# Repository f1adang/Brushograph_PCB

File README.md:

# Brushograph PCB

This repository contains the KiCad PCB design files for the Brushograph (miniPenzlograf) project, a pen-plotting device designed for creating artistic drawings and patterns.

**A manufacturing-ready PCB-design to run FluidNC on ESP32 including ULN2003 drivers for 3 uni-polar stepper motors (28byj-48)**

**A DIY etchable PCB-design to run FluidNC on ESP32 including ULN2003 drivers for 3 uni-polar stepper motors (28byj-48)**

## About Brushograph

This PCB repository is part of the larger Brushograph project, which explores "Ways of painting with a mechatronic brush" - an intersection between classical artistic techniques and modern technology.

**Main Documentation:**
- [Brushograph Wiki](https://wiki.sgmk-ssam.ch/wiki/Brushograph) - Complete project documentation

## Project Structure

- `Brusograf_PCB/` - Original KiCad project (DIY etchable, single layer)
  - `MASK/` - Mask files in SVG and PDF for PCB silkscreen
- `Brushograf_PCB-china/` - Rev A: manufacturing-ready project and Gerbers
  - `Gerber_Brusograf_black.zip` - Zipped Gerbers ready to upload to a PCB manufacturer
- `Brushograf_PCB-revB/` - Rev B: work in progress (see "Rev B" below)
- `FluidNC_config/` - Configuration for FluidNC firmware
  - `config_pink.yaml` - Rev A config
  - `config_revB.yaml` - Rev B config, adds the pendant UART
- `photos/` - Project photos and documentation images

## Rev B (in progress)

`Brushograf_PCB-revB/` replaces the power section with a USB-C Power Delivery
supply feeding an adjustable motor rail, and adds a pendant port and an ESP
power switch.

**Schematic: complete and verified. PCB: all parts placed, routing still to do.**

The board grows from **198 x 48mm to 198 x 73mm** - 25mm added along the top
edge. Everything from rev A keeps its coordinates; all the new parts live in
the new strip. The RJ-12 needs about 19mm of depth behind the top edge and the
old board only had 11mm before the back-side SPI tracks, which is what forced
the growth.

### What rev B adds

**USB-C Power Delivery is now the only power inlet.** The barrel jack is gone,
along with its reverse-polarity FET and zener. J12 sits on the **left edge**
with the receptacle overhanging it; a CH224K sink controller (U6) requests
**9V**, set by the single 6.8k resistor R24 on CFG1 per the WCH datasheet. A
"PD OK" LED (D17) on the controller's power-good output shows when the contract
is up. VBUS reaches the converters through a 1.5A resettable fuse (F1).

PD offers no 7.5V fixed profile, so the 9V rail feeds two buck converters.

**Adjustable motor rail.** U7 (TPS54202, 2A) steps 9V down to the motor rail,
adjustable with trimmer RV1 over roughly **5.4 - 8.6V**, nominally 7.5V. The
divider is 100k on top and 7.5k plus the 10k trimmer below, against the
TPS54202's 0.596V reference. The wiper is tied to the top of the track, so a
lifted wiper drops the output rather than raising it.

> Running 5V-rated 28BYJ-48 motors at 7.5V is a deliberate overclock: about
> 300mA per motor with two phases energised, roughly 900mA for three. More
> torque and speed, but the motors will run noticeably warm. Set the trimmer to
> 5V first and work up.

**Separate 5V logic rail.** U8 (TPS54202) makes 5.07V for the ESP32. The DevKitC
cannot be fed 7.5V on its 5V pin - its onboard AMS1117 would burn about a watt -
so logic and motors get separate rails.

**ESP power switch.** SW1 is a panel **lever switch on the left edge**, actuator
overhanging the board. It is a 1P2T part used as a simple break: common to the
ESP32, one throw to the board's 5V, the other left open, so the far position
leaves the module running on its own USB supply while the rest of the board
stays powered. D14 (SS14) blocks USB 5V from back-feeding the logic buck.

**RJ-12 pendant port** on the **upper edge**, opening facing off the board. J13
brings UART1 out on GPIO 2 and 15 with switched 5V, behind a 0.5A resettable
fuse (F2), 330R series resistors and TVS clamps.

**J7 repurposed.** Pin 3 used to carry the raw barrel-jack rail straight to the
motors, which would have destroyed them with a 12V adapter. It now carries the
regulated adjustable rail; pin 1 is the 5V logic rail for testing, pin 2 the
motor rail.

### Status

| Area | State |
|---|---|
| Schematic | Complete. 75 parts, 120 nets, netlist verified net by net |
| ERC | At or below rev A in every category |
| Placement | All 36 new footprints placed, zones refilled |
| DRC | No new errors except on J12 - see below |
| Routing | **53 ratsnest connections outstanding** |

### Known DRC findings

- **J12 reports 27 `shorting_items` and 4 `hole_clearance` errors.** These are
  not caused by the placement: the same 31 errors appear with the untouched
  stock footprint alone on an otherwise empty board. The pads have genuine
  0.2-0.7mm gaps and nothing bridges them - zones, solder mask and neighbouring
  copper were each ruled out by experiment. Every USB-C footprint in the KiCad
  library has sub-0.25mm pad gaps, so swapping parts will not help. Worth
  opening in the GUI, where the marker shows interactively what it thinks is
  touching, before committing to fab.
- `allow_soldermask_bridges` is set on J12, which is the correct treatment for a
  fine-pitch connector and clears 23 mask-bridge errors.
- Everything else - 4 mounting-hole annular widths, U4's malformed courtyard,
  5 starved thermals - is inherited unchanged from rev A.

### Open questions

- **The RJ-12 pin order is unverified.** The board uses
  `1 = GND, 2 = +5V, 3 = TX, 4 = RX, 5 = +5V, 6 = GND`, chosen so a standard
  reversing modular cable keeps power and ground on the right contacts and swaps
  TX/RX. bdring's official FluidDial pinout could not be confirmed from public
  documentation - **check it against your cable before building**.
- GPIO2 is an ESP32 strapping pin. It must not be pulled high during boot or the
  chip enters download mode. An idle-high UART receiver at the pendant end is
  fine; anything that actively drives the line is not.

### Known issues carried over from rev A

- The `MISO` and `MOSI` net names are swapped relative to the SD card: net
  `MISO` (GPIO19) goes to the card's CMD/DI pin, which is physically MOSI. The
  card works and the FluidNC config is correct, but **J6's back silkscreen is
  mislabelled** - an external SD module wired to J6 per the silk will have DI
  and DO reversed.
- R1-R12 and C1-C3 still have no values in the schematic, so the BOM is not
  directly orderable.
- The four mounting holes are plated pads with zero annular ring and should be
  non-plated.

## Features

- Custom PCB design for the Brushograph device
- ESP32-based control board with FluidNC firmware support
- Integrated ULN2003 drivers for 3 uni-polar stepper motors (28byj-48)
- DIY etchable single-layer design for easy home fabrication
- Rounded PCB version available
- Configuration files for FluidNC firmware (custom fork for support uni-polar steppers)

## Hardware Configuration

### ESP32 Pin Configuration

Phase order below matches `FluidNC_config/config_revB.yaml`. Note it is the
reverse of what older revisions of this README listed - reversing the phase
order simply reverses the direction of travel.

#### X-Axis Motor (Unipolar)
- Phase 0: GPIO 27
- Phase 1: GPIO 14
- Phase 2: GPIO 13
- Phase 3: GPIO 4

#### Y-Axis Motor (Unipolar)
- Phase 0: GPIO 22
- Phase 1: GPIO 21
- Phase 2: GPIO 17
- Phase 3: GPIO 16

#### Z-Axis Motor (Unipolar)
- Phase 0: GPIO 32
- Phase 1: GPIO 33
- Phase 2: GPIO 25
- Phase 3: GPIO 26

#### SD Card (SPI)
- MOSI: GPIO 19  (net labelled `MISO` on the schematic - see Known issues)
- MISO: GPIO 23  (net labelled `MOSI` on the schematic - see Known issues)
- SCK: GPIO 18
- CS: GPIO 5

#### Pendant UART (rev B)
- TX: GPIO 2 (J13)
- RX: GPIO 15 (J13)

#### Still free
GPIO 34, 35, 36 and 39 (all input-only), GPIO 12, and UART0 on GPIO 1/3.

The four input-only pins are the natural place for limit switches if homing is
added later; they have no internal pull-ups, so each would need an external one.

### Motor Configuration

`config_revB.yaml` in the FluidNC_config directory carries the settings for the
stepper motors. There are no limit switches, so no homing cycles are defined and
every limit pin is `NO_PIN`:

- X/Y axis: 93 steps/mm, 1500 mm/min max rate, 80 mm/s2 acceleration
- Z axis: 108 steps/mm, 1000 mm/min max rate, 40 mm/s2 acceleration

### 28BYJ-48 Stepper Motors

The PCB is designed specifically for the commonly available and inexpensive 28BYJ-48 unipolar stepper motors:
- 5V DC operation
- Gear reduction ratio of 1:64
- Step angle of 5.625° (64 steps per revolution)
- 4-phase operation via ULN2003 driver

## Getting Started

To view or modify the PCB design:
1. Install KiCad (version 6.0 or later recommended)
2. Open the `.kicad_pro` project file in the `Brusograf_PCB` directory
     - For the latest manufacturing-ready version, you can also open the project in `Brushograf_PCB-china/`

For complete setup instructions, including firmware and mechanical assembly, please refer to the [Brushograph Wiki](https://wiki.sgmk-ssam.ch/wiki/Brushograph).

## Manufacturing-ready files

- Latest Gerbers (ZIP, ready for fab): [`Brushograf_PCB-china/Gerber_Brusograf_black.zip`](Brushograf_PCB-china/Gerber_Brusograf_black.zip)
- Gerber folder (all layers and drill files): [`Brushograf_PCB-china/Gerber_Brusograf/`](Brushograf_PCB-china/Gerber_Brusograf/)

## Related Repositories

- [FluidNC for unipolar steppers](https://git.kompot.si/g1smo/FluidNC) - Forked and reworked version of FluidNC to support uni-polar steppers

## License

[Specify license here]

## Credits

Designed by dusjagr

The Brushograph project is based on Dominik Mahnič's "Brušografia" concept, bridging traditional painting and technology.

## Contact

[Your contact information here]

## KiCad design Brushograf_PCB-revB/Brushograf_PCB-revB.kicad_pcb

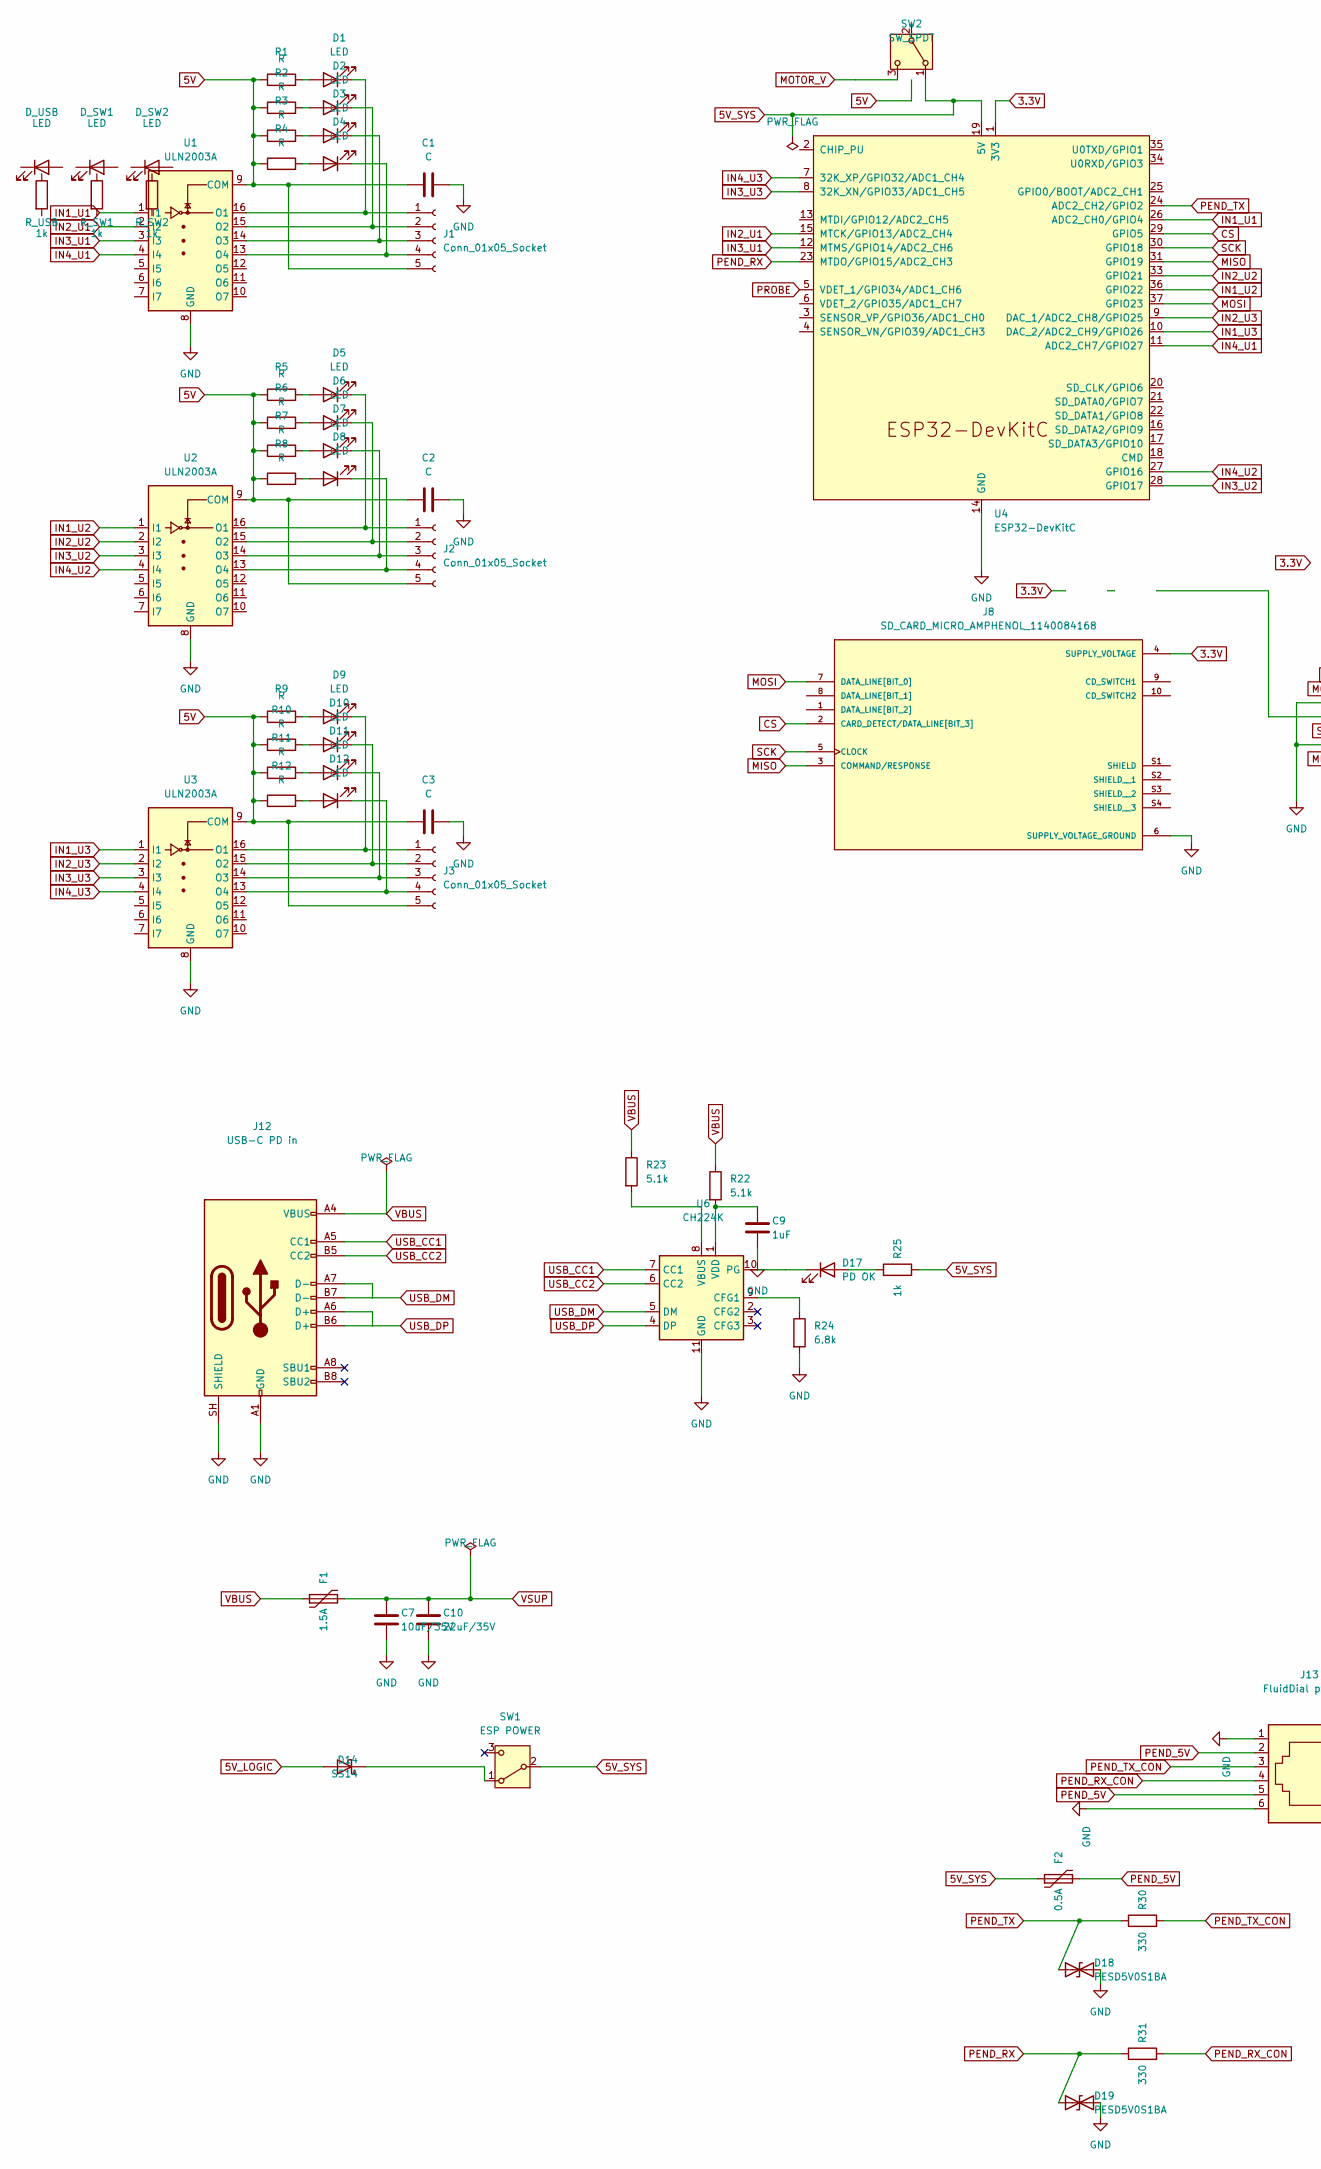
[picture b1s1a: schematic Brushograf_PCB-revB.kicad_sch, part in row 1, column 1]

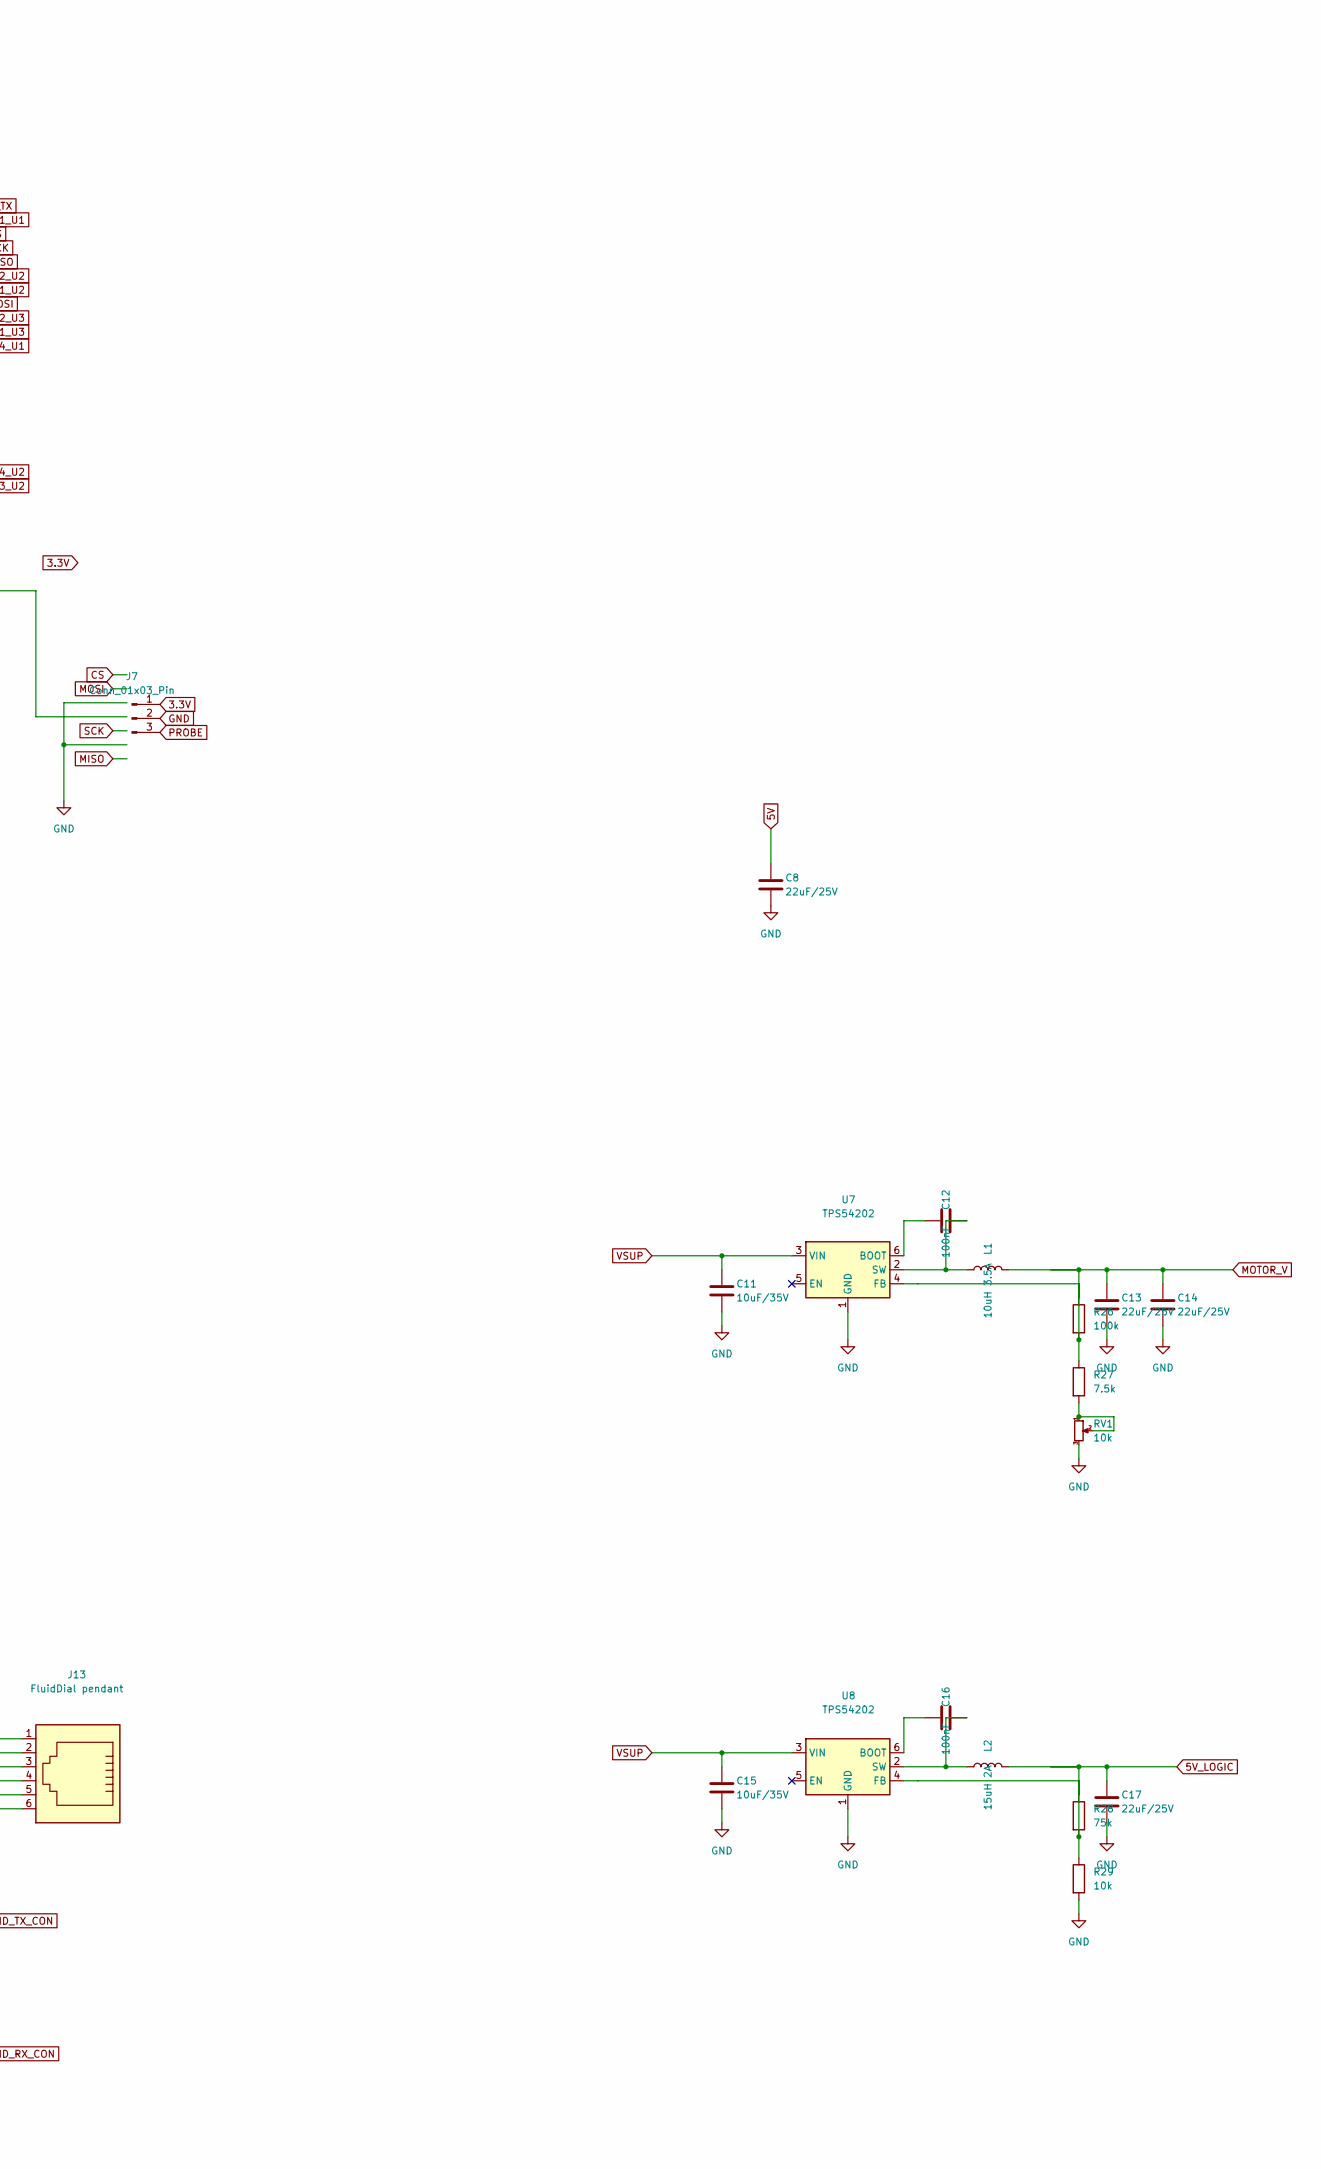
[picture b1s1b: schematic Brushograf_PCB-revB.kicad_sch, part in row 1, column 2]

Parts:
C1, C2, C3: C; C_1210_noGND
C7: 10uF/35V; C_1206_3216Metric_Pad1.33x1.80mm_HandSolder
C8, C13, C14, C17: 22uF/25V; C_1210_3225Metric_Pad1.33x2.70mm_HandSolder
C9: 1uF; C_0603_1608Metric_Pad1.08x0.95mm_HandSolder
C10: 22uF/35V; C_1210_3225Metric_Pad1.33x2.70mm_HandSolder
C11, C15: 10uF/35V; C_1210_3225Metric_Pad1.33x2.70mm_HandSolder
C12, C16: 100nF; C_0603_1608Metric_Pad1.08x0.95mm_HandSolder
D1, D2, D3, D4, D5, D6, D7, D8, D9, D10, D11, D12: LED; LED_D1.8mm_W3.3mm_H2.4mm
D14: SS14; D_SMA_Handsoldering
D17: PD OK; LED_0805_2012Metric_Pad1.15x1.40mm_HandSolder
D18, D19: PESD5V0S1BA; D_SOD-323
D_SW1, D_SW2: LED; LED_D1.8mm_Brushograf
D_USB: LED; LED_D1.8mm_Brushograf
F1: 1.5A; Fuse_1812_4532Metric_Pad1.30x3.40mm_HandSolder
F2: 0.5A; Fuse_1206_3216Metric_Pad1.42x1.75mm_HandSolder
J1, J2, J3: Conn_01x05_Socket; Molex_1x05_P2.54mm_Vertical
J7: Conn_01x03_Pin; PinHeader_1x03_P2.54mm_Vertical
J8: SD_CARD_MICRO_AMPHENOL_1140084168; PARTREV A
J12: USB-C PD in; USB_C_Receptacle_GCT_USB4105-xx-A_16P_TopMnt_Horizontal
J13: FluidDial pendant; RJ12_Amphenol_54601-x06_Horizontal
L1: 10uH 3.5A; L_7.3x7.3_H4.5
L2: 15uH 2A; L_7.3x7.3_H4.5
R1, R2, R3, R4, R5, R6, R7, R8, R9, R10, R11, R12: R; R_1206_noGND
R22, R23: 5.1k; R_0603_1608Metric_Pad0.98x0.95mm_HandSolder
R24: 6.8k; R_0603_1608Metric_Pad0.98x0.95mm_HandSolder
R25: 1k; R_0603_1608Metric_Pad0.98x0.95mm_HandSolder
R26: 100k; R_0603_1608Metric_Pad0.98x0.95mm_HandSolder
R27: 7.5k; R_0603_1608Metric_Pad0.98x0.95mm_HandSolder
R28: 75k; R_0603_1608Metric_Pad0.98x0.95mm_HandSolder
R29: 10k; R_0603_1608Metric_Pad0.98x0.95mm_HandSolder
R30, R31: 330; R_0603_1608Metric_Pad0.98x0.95mm_HandSolder
RV1: 10k; Potentiometer_Bourns_3296W_Vertical
R_SW1, R_SW2: 1k; R_1206_noGND
R_USB: 1k; R_1206_noGND
SW1: ESP POWER; SW_Lever_1P2T_NKK_GW12LxH
SW2: SW_SPDT; SW_Slide_1P2T_EG1218
U1, U2, U3: ULN2003A; DIP-16_W7.62mm_Socket_LongPads
U4: ESP32-DevKitC; ESP32-DevKitC_mod
U6: CH224K; SSOP-10-1EP_3.9x4.9mm_P1mm_EP2.1x3.3mm
U7, U8: TPS54202; SOT-23-6

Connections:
3.3V: J7.1, J8.4 (SUPPLY_VOLTAGE), U4.1 (3V3)
5V: C1.1, C2.1, C3.1, C8.1, J1.5, J2.5, J3.5, R1.1, R2.1, R3.1, R4.1, R5.1, R6.1, R7.1, R8.1, R9.1, R10.1, R11.1, R12.1, R_SW2.1, SW2.2 (B), U1.9 (COM), U2.9 (COM), U3.9 (COM); also elsewhere on the board
5V_LOGIC: C17.1, D14.2 (A), L2.2, R28.1; also elsewhere on the board
5V_SYS: F2.1, R25.2, R_SW1.1, SW1.2 (B), SW2.1 (A), U4.19 (5V)
CS: J8.2 (CARD_DETECT/DATA_LINE[BIT_3]), U4.29 (GPIO5)
GND: C1.2, C2.2, C3.2, C7.2, C8.2, C9.2, C10.2, C11.2, C13.2, C14.2, C15.2, C17.2, D18.2 (A2), D19.2 (A2), D_SW1.2 (A), D_SW2.2 (A), D_USB.2 (A), J7.2, J8.6 (SUPPLY_VOLTAGE_GROUND), J12.A1 (GND), J12.A12 (GND), J12.B1 (GND), J12.B12 (GND), J12.SH (SHIELD), J13.1, J13.6, R24.2, R29.2, RV1.3, U1.8 (GND), U2.8 (GND), U3.8 (GND), U4.14 (GND), U4.32 (GND), U4.38 (GND), U6.11 (GND), U7.1 (GND), U8.1 (GND); also elsewhere on the board
IN1_U1: U1.1 (I1), U4.26 (ADC2_CH0/GPIO4); also elsewhere on the board
IN1_U2: U2.1 (I1), U4.36 (GPIO22); also elsewhere on the board
IN1_U3: U3.1 (I1), U4.10 (DAC_2/ADC2_CH9/GPIO26); also elsewhere on the board
IN2_U1: U1.2 (I2), U4.15 (MTCK/GPIO13/ADC2_CH4); also elsewhere on the board
IN2_U2: U2.2 (I2), U4.33 (GPIO21); also elsewhere on the board
IN2_U3: U3.2 (I2), U4.9 (DAC_1/ADC2_CH8/GPIO25); also elsewhere on the board
IN3_U1: U1.3 (I3), U4.12 (MTMS/GPIO14/ADC2_CH6); also elsewhere on the board
IN3_U2: U2.3 (I3), U4.28 (GPIO17); also elsewhere on the board
IN3_U3: U3.3 (I3), U4.8 (32K_XN/GPIO33/ADC1_CH5); also elsewhere on the board
IN4_U1: U1.4 (I4), U4.11 (ADC2_CH7/GPIO27); also elsewhere on the board
IN4_U2: U2.4 (I4), U4.27 (GPIO16); also elsewhere on the board
IN4_U3: U3.4 (I4), U4.7 (32K_XP/GPIO32/ADC1_CH4); also elsewhere on the board
MISO: J8.3 (COMMAND/RESPONSE), U4.31 (GPIO19)
MOSI: J8.7 (DATA_LINE[BIT_0]), U4.37 (GPIO23)
unnamed: D1.1 (K), J1.1, U1.16 (O1)
unnamed: D2.2 (A), R2.2
unnamed: D2.1 (K), J1.2, U1.15 (O2)
unnamed: D3.2 (A), R3.2
unnamed: D3.1 (K), J1.3, U1.14 (O3)
unnamed: D4.2 (A), R4.2
unnamed: D4.1 (K), J1.4, U1.13 (O4)
unnamed: D5.2 (A), R5.2
unnamed: D5.1 (K), J2.1, U2.16 (O1)
unnamed: D6.2 (A), R6.2
unnamed: D6.1 (K), J2.2, U2.15 (O2)
unnamed: D7.2 (A), R7.2
unnamed: D7.1 (K), J2.3, U2.14 (O3)
unnamed: D8.2 (A), R8.2
unnamed: D8.1 (K), J2.4, U2.13 (O4)
unnamed: D9.2 (A), R9.2
unnamed: D9.1 (K), J3.1, U3.16 (O1)
unnamed: D10.2 (A), R10.2
unnamed: D10.1 (K), J3.2, U3.15 (O2)
unnamed: D11.2 (A), R11.2
unnamed: D11.1 (K), J3.3, U3.14 (O3)
unnamed: D12.2 (A), R12.2
unnamed: D12.1 (K), J3.4, U3.13 (O4)
unnamed: D14.1 (K), SW1.1 (A)
unnamed: D17.2 (A), R25.1
unnamed: D17.1 (K), U6.10 (PG)
unnamed: D_SW1.1 (K), R_SW1.2
unnamed: D_SW2.1 (K), R_SW2.2
unnamed: D_USB.1 (K), R_USB.2
unnamed: R27.2, RV1.1, RV1.2
unnamed: R24.1, U6.9 (CFG1)
unnamed: R23.2, U6.8 (VBUS)
unnamed: C9.1, R22.2, U6.1 (VDD)
unnamed: C12.1, U7.6 (BOOT)
unnamed: R26.2, R27.1, U7.4 (FB)
unnamed: C12.2, L1.1, U7.2 (SW)
unnamed: C16.1, U8.6 (BOOT)
unnamed: R28.2, R29.1, U8.4 (FB)
unnamed: C16.2, L2.1, U8.2 (SW)
PEND_5V: F2.2, J13.2, J13.5
PEND_RX: D19.1 (A1), R31.1, U4.23 (MTDO/GPIO15/ADC2_CH3)
PEND_RX_CON: J13.4, R31.2
PEND_TX: D18.1 (A1), R30.1, U4.24 (ADC2_CH2/GPIO2)
PEND_TX_CON: J13.3, R30.2
PROBE: J7.3, U4.5 (VDET_1/GPIO34/ADC1_CH6)
SCK: J8.5 (CLOCK), U4.30 (GPIO18)
USB_CC1: J12.A5 (CC1), U6.7 (CC1)
USB_CC2: J12.B5 (CC2), U6.6 (CC2)
USB_DM: J12.A7 (D-), J12.B7 (D-), U6.5 (DM)
USB_DP: J12.A6 (D+), J12.B6 (D+), U6.4 (DP)
VBUS: F1.1, J12.A4 (VBUS), J12.A9 (VBUS), J12.B4 (VBUS), J12.B9 (VBUS), R22.1, R23.1, R_USB.1
VSUP: C7.1, C10.1, C11.1, C15.1, F1.2, U7.3 (VIN), U8.3 (VIN)

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
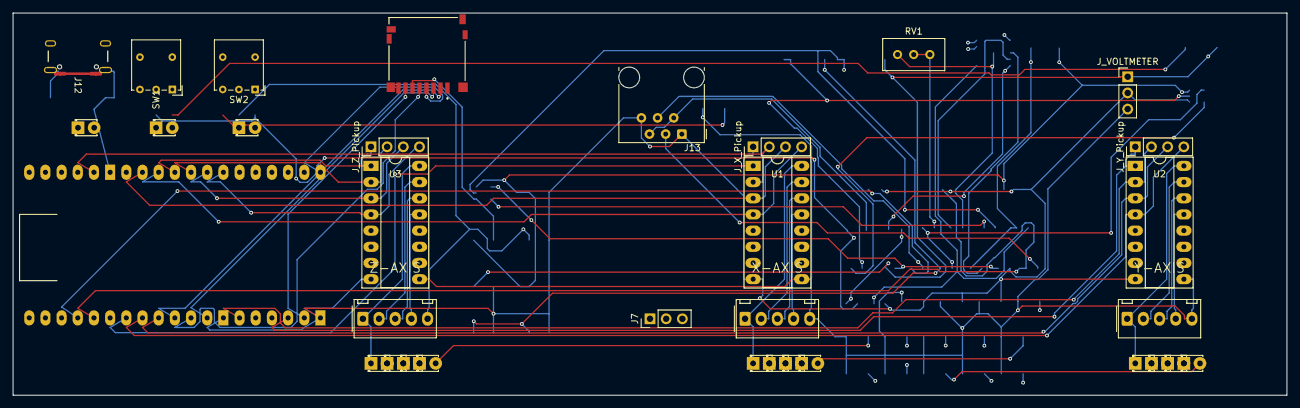
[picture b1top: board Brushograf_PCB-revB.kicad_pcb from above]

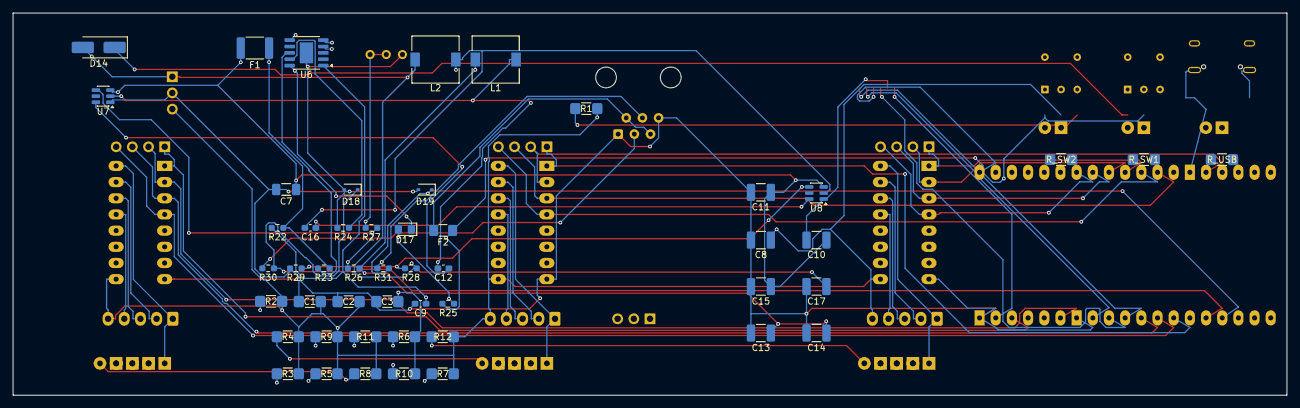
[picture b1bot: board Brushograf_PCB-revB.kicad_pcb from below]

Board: 2 copper layers, 200.0 x 60.0 mm, 83 parts (50 on the bottom side), 73 nets.

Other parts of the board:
J_VOLTMETER: PinHeader_1x03_P2.54mm_Vertical
J_X_Pickup: PinHeader_1x04_P2.54mm_Vertical
J_Y_Pickup: PinHeader_1x04_P2.54mm_Vertical
J_Z_Pickup: PinHeader_1x04_P2.54mm_Vertical

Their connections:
5V: J_VOLTMETER.3; also elsewhere on the board
5V_LOGIC: J_VOLTMETER.1; also elsewhere on the board
GND: J_VOLTMETER.2; also elsewhere on the board
IN1_U1: J_X_Pickup.1; also elsewhere on the board
IN1_U2: J_Y_Pickup.1; also elsewhere on the board
IN1_U3: J_Z_Pickup.1; also elsewhere on the board
IN2_U1: J_X_Pickup.2; also elsewhere on the board
IN2_U2: J_Y_Pickup.2; also elsewhere on the board
IN2_U3: J_Z_Pickup.2; also elsewhere on the board
IN3_U1: J_X_Pickup.3; also elsewhere on the board
IN3_U2: J_Y_Pickup.3; also elsewhere on the board
IN3_U3: J_Z_Pickup.3; also elsewhere on the board
IN4_U1: J_X_Pickup.4; also elsewhere on the board
IN4_U2: J_Y_Pickup.4; also elsewhere on the board
IN4_U3: J_Z_Pickup.4; also elsewhere on the board

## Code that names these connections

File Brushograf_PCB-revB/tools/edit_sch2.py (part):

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    raise SystemExit('ERROR: J7 5V-EXT label not found')

# pendant UART out to the ESP32
sh.wire(157.48, 57.15, 152.4, 57.15)          # U4 pin 23, GPIO15
sh.label('PEND_RX', 152.4, 57.15, 180)
sh.wire(223.52, 46.99, 228.6, 46.99)          # U4 pin 24, GPIO2
sh.label('PEND_TX', 228.6, 46.99, 0)

# =====================================================  USB-C + CH224K PD sink
J12 = sh.place('Connector', 'USB_C_Receptacle_USB2.0_16P', 'J12', 'USB-C PD in',
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sh.junction(97.79, YB)
sh.wire(97.79, YB, 97.79, YB - 7.62)
sh.pwrflag(97.79, YB - 7.62, 0)
sh.label('VSUP', 105.0, YB, 0)

# =====================================================  buck converters
def buck(ref_u, X, Y, vout_net, l_ref, l_val, cin_ref, cb_ref, cout_refs,
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                 ref_at=(X, Y - 12.7, None), val_at=(X, Y - 10.16, None))
    vin = U.p('VIN')
    sh.wire(vin[0] - 25.4, vin[1], *vin)
    sh.label('VSUP', vin[0] - 25.4, vin[1], 180)
    Cin = sh.place('Device', 'C', cin_ref, cin_val, C1210, vin[0] - 12.7, vin[1] + 6.35, 0)
    sh.wire(vin[0] - 12.7, vin[1], *Cin.p('1'))
    sh.junction(vin[0] - 12.7, vin[1])
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YP = 330.0
J13 = sh.place('Connector', 'RJ12', 'J13', 'FluidDial pendant', RJ12FP, 250, YP, 180,
               ref_at=(250, YP - 16.51, None), val_at=(250, YP - 13.97, None))
PEND_PINS = [('1', 'GND', 5.08), ('2', 'PEND_5V', 10.16), ('3', 'PEND_TX_CON', 15.24),
             ('4', 'PEND_RX_CON', 20.32), ('5', 'PEND_5V', 25.4), ('6', 'GND', 30.48)]
for pin, net, ln in PEND_PINS:
    px, py = J13.p(pin)
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sh.wire(F2.p('1')[0] - 7.62, F2.p('1')[1], *F2.p('1'))
sh.label('5V_SYS', F2.p('1')[0] - 7.62, F2.p('1')[1], 180)
sh.wire(*F2.p('2'), F2.p('2')[0] + 7.62, F2.p('2')[1])
sh.label('PEND_5V', F2.p('2')[0] + 7.62, F2.p('2')[1], 0)

# UART lines: series resistor plus a TVS clamp on each, as on the official module
for pin_net, gpio_net, rref, dref, ry in (
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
